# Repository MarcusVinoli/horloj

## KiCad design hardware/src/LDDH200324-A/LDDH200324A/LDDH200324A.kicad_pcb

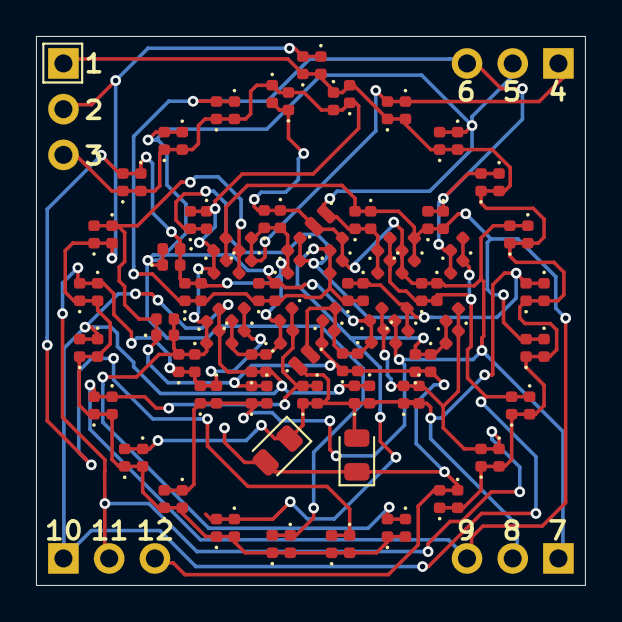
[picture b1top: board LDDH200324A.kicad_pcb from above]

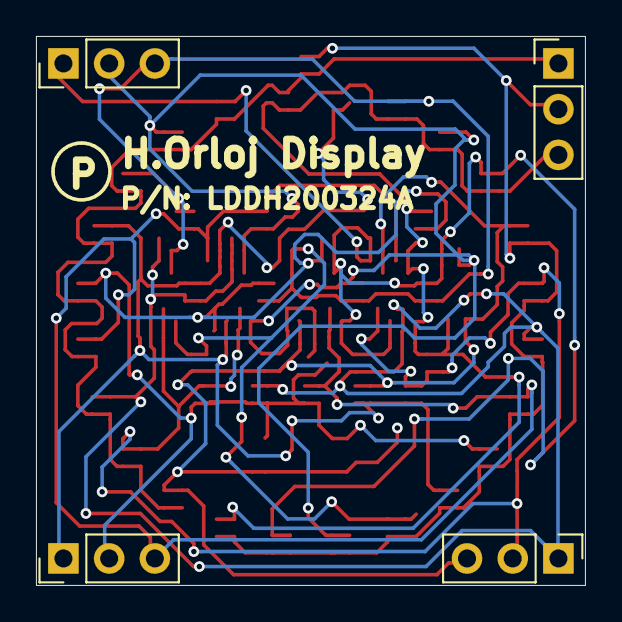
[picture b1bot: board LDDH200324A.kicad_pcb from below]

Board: 2 copper layers, 30.5 x 30.5 mm, 126 parts (4 on the bottom side), 12 nets.

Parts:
D1, D3, D5, D7, D9, D11, D13, D15, D17, D19, D21, D23, D25, D27, D29, D31, D33, D35, D37, D39, D41, D43, D45, D47, D49, D55, D56, D57, D58, D59, D61, D63, D65, D67, D69, D71, D73, D75, D81, D82, D83, D84, D85, D87, D89, D91, D93, D95, D97, D99, D101, D107, D108, D109, D110, D111, D113, D115, D117, D119: RED; LED_0402_1005Metric
D2, D4, D6, D8, D10, D12, D14, D16, D18, D20, D22, D24, D26, D28, D30, D32, D34, D36, D38, D40, D42, D44, D46, D48, D50, D51, D52, D53, D54, D60, D62, D64, D66, D68, D70, D72, D74, D76, D77, D78, D79, D80, D86, D88, D90, D92, D94, D96, D98, D100, D102, D103, D104, D105, D106, D112, D114, D116, D118, D120: GREEN; LED_0402_1005Metric
D121: RED; LED_0805_2012Metric
D122: GREEN; LED_0805_2012Metric
J1, J2, J3, J4: Conn_01x03; PinHeader_1x03_P2.54mm_Vertical

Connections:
PIN_01: D1.1, D2.2, D5.1, D6.2, D9.1, D10.2, D13.1, D14.2, D17.1, D18.2, D21.1, D22.2, D25.1, D26.2, D29.1, D30.2, D33.1, D34.2, D37.1, D38.2, D41.1, D42.2, J1.1
PIN_02: D1.2, D2.1, D19.1, D20.2, D23.1, D24.2, D27.1, D28.2, D31.1, D32.2, D35.1, D36.2, D39.1, D40.2, D43.1, D44.2, D45.1, D46.2, D47.1, D48.2, D49.1, D50.2, J1.2
PIN_03: D3.1, D4.2, D5.2, D6.1, D7.1, D8.2, D11.1, D12.2, D15.1, D16.2, D45.2, D46.1, D51.2, D55.1, D61.1, D62.2, D85.1, D86.2, D87.1, D88.2, D103.2, D107.1, J1.3
PIN_04: D9.2, D10.1, D15.2, D16.1, D49.2, D50.1, D52.2, D56.1, D59.1, D60.2, D63.1, D64.2, D65.1, D66.2, D77.2, D81.1, D89.1, D90.2, D91.1, D92.2, D104.2, D108.1, J2.1
PIN_05: D11.2, D12.1, D13.2, D14.1, D47.2, D48.1, D53.2, D57.1, D59.2, D60.1, D67.1, D68.2, D71.1, D72.2, D78.2, D82.1, D93.1, D94.2, D95.1, D96.2, D97.1, D98.2, D105.2, D109.1, J2.2
PIN_06: D7.2, D8.1, D17.2, D18.1, D43.2, D44.1, D54.2, D58.1, D69.1, D70.2, D75.1, D76.2, D77.1, D78.1, D79.2, D81.2, D82.2, D83.1, D101.1, D102.2, D106.2, D110.1, J2.3
PIN_07: D3.2, D4.1, D21.2, D22.1, D39.2, D40.1, D52.1, D56.2, D67.2, D68.1, D69.2, D70.1, D73.1, D74.2, D80.2, D84.1, D99.1, D100.2, D111.1, D112.2, D113.1, D114.2, J3.1
PIN_08: D25.2, D26.1, D35.2, D36.1, D51.1, D55.2, D65.2, D66.1, D79.1, D83.2, D93.2, D94.1, D99.2, D100.1, D115.1, D116.2, D117.1, D118.2, D119.1, D120.2, D121.1, D122.2, J3.2
PIN_09: D29.2, D30.1, D31.2, D32.1, D53.1, D54.1, D57.2, D58.2, D61.2, D62.1, D73.2, D74.1, D91.2, D92.1, D115.2, D116.1, J3.3
PIN_10: D27.2, D28.1, D33.2, D34.1, D71.2, D72.1, D75.2, D76.1, D80.1, D84.2, D87.2, D88.1, D104.1, D108.2, D117.2, D118.1, J4.1
PIN_11: D23.2, D24.1, D37.2, D38.1, D89.2, D90.1, D97.2, D98.1, D101.2, D102.1, D103.1, D107.2, D111.2, D112.1, D119.2, D120.1, J4.2
PIN_12: D19.2, D20.1, D41.2, D42.1, D63.2, D64.1, D85.2, D86.1, D95.2, D96.1, D105.1, D106.1, D109.2, D110.2, D113.2, D114.1, D121.2, D122.1, J4.3

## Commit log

2020-03-19 Commit inicial do repositório.
2020-03-19 Insere prévia do Mapa de LEDs no arquivo Sketches.cdr.
2020-03-20 Inicia a implementação do Display.
2020-03-22 Insere MockUps digitais e inicia o projeto da PCB.
2020-03-28 Insere mockups do produto final. Inicia o projeto do display.
2020-04-01 Inicia a implementação do firmware. Implementa a Biblioteca de RTC.
2020-04-02 Atualiza o modelo do Display. Inicia a implementação da biblioteca de Charlieplexing.
2020-04-03 Inicia a implementação da Estrutura de Dados do display.
2020-04-03 Atualiza os rascunhos para o novo modelo de display.
2020-04-10 Insere o arquivo .gitignore.txt.
2020-04-10 Organiza a pasta de desenhos e mock-ups do protótipo.
2020-04-10 Inicia a implementação da biblioteca de charlieplexação.
2020-04-10 Modifica o pinout do MCU.
2020-04-10 Alterações no projeto do firmware.
2020-04-12 Atualiza o pinout do microcontrolador. Implementa arquivo de simulação do hardware.
2020-04-12 Implementa a biblioteca de Charlieplexação do display.
2020-04-12 Corrige o bug da biblioteca de charlieplexação.
